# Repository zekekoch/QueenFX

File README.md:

# QueenFX

LED effects for the Queen art car. A Teensy 3.2 drives 16 LED tubes
with FastLED. Effects are selected from the dashboard's 8 lit
buttons (but supports 16), which are read through a 4067 multiplexer and lit by
TLC59711 LED drivers.

## Files

- `QueenFX.ino`: the main sketch. It holds the tube layout, the
  effects, and the button-to-effect mapping in `loop()`.
- `Buttons.h`: dashboard buttons. It reads them through the mux and
  sets their colors through the TLC59711 boards.
- `Mux.h`: reads the 4067 multiplexer that the buttons and dials are
  wired to.
- `hardware/`: the controller board (QueenController 2022b), in Eagle
  9.6 format.
  - `queencontroller2022.sch`: schematic.
  - `queencontroller2022.brd`: board layout.
  - `queencontroller2022.pdf`: a mirrored print of the board layout,
    from Apr 10, 2022. The `.brd` was edited after that (Aug 7, 2022),
    so the print may not match it.

## Setup

### 1. Arduino IDE

Install [Arduino IDE 2.x](https://www.arduino.cc/en/software).

### 2. Teensyduino (Teensy board support)

1. Open **Arduino IDE → Settings** (Preferences on Windows/Linux).
2. Add this URL to **Additional boards manager URLs**:

   ```
   https://www.pjrc.com/teensy/package_teensy_index.json
   ```

3. Open **Tools → Board → Boards Manager**, search for **Teensy**, and
   install **Teensy (for Arduino IDE 2.0.4 or later)**.

PJRC's instructions are at
<https://www.pjrc.com/teensy/td_download.html>.

### 3. Libraries

Install these from **Tools → Manage Libraries**:

| Library | Used by | Notes |
|---|---|---|
| FastLED | `QueenFX.ino`, `Buttons.h` | Teensyduino also bundles a copy |
| Adafruit TLC59711 | `Buttons.h` | Install its dependencies when prompted |
| Adafruit BusIO | Adafruit TLC59711 | Usually installed as a dependency |

### 4. Board settings

Under **Tools**, set:

- **Board:** Teensy 3.2 / 3.1
- **USB Type:** Serial
- **Port:** the Teensy's port

Then compile and upload. The Teensy Loader app opens automatically
during upload. If it doesn't program the board, press the button on
the Teensy.

## Hardware notes

- **LED outputs:** FastLED's parallel output on port D and port C
  gives 8 + 8 = 16 outputs (`addLeds<WS2811_PORTD,8>` and
  `addLeds<WS2811_PORTC,8>` in `setup()`).
- **TLC59711 button lights:** 4 chained boards, data on pin 4, clock
  on pin 3.
- **4067 mux:** select pins A=17, B=18, C=A11, D=19; signal pin Z=A2.
- **Serial monitor:** 57600 baud.

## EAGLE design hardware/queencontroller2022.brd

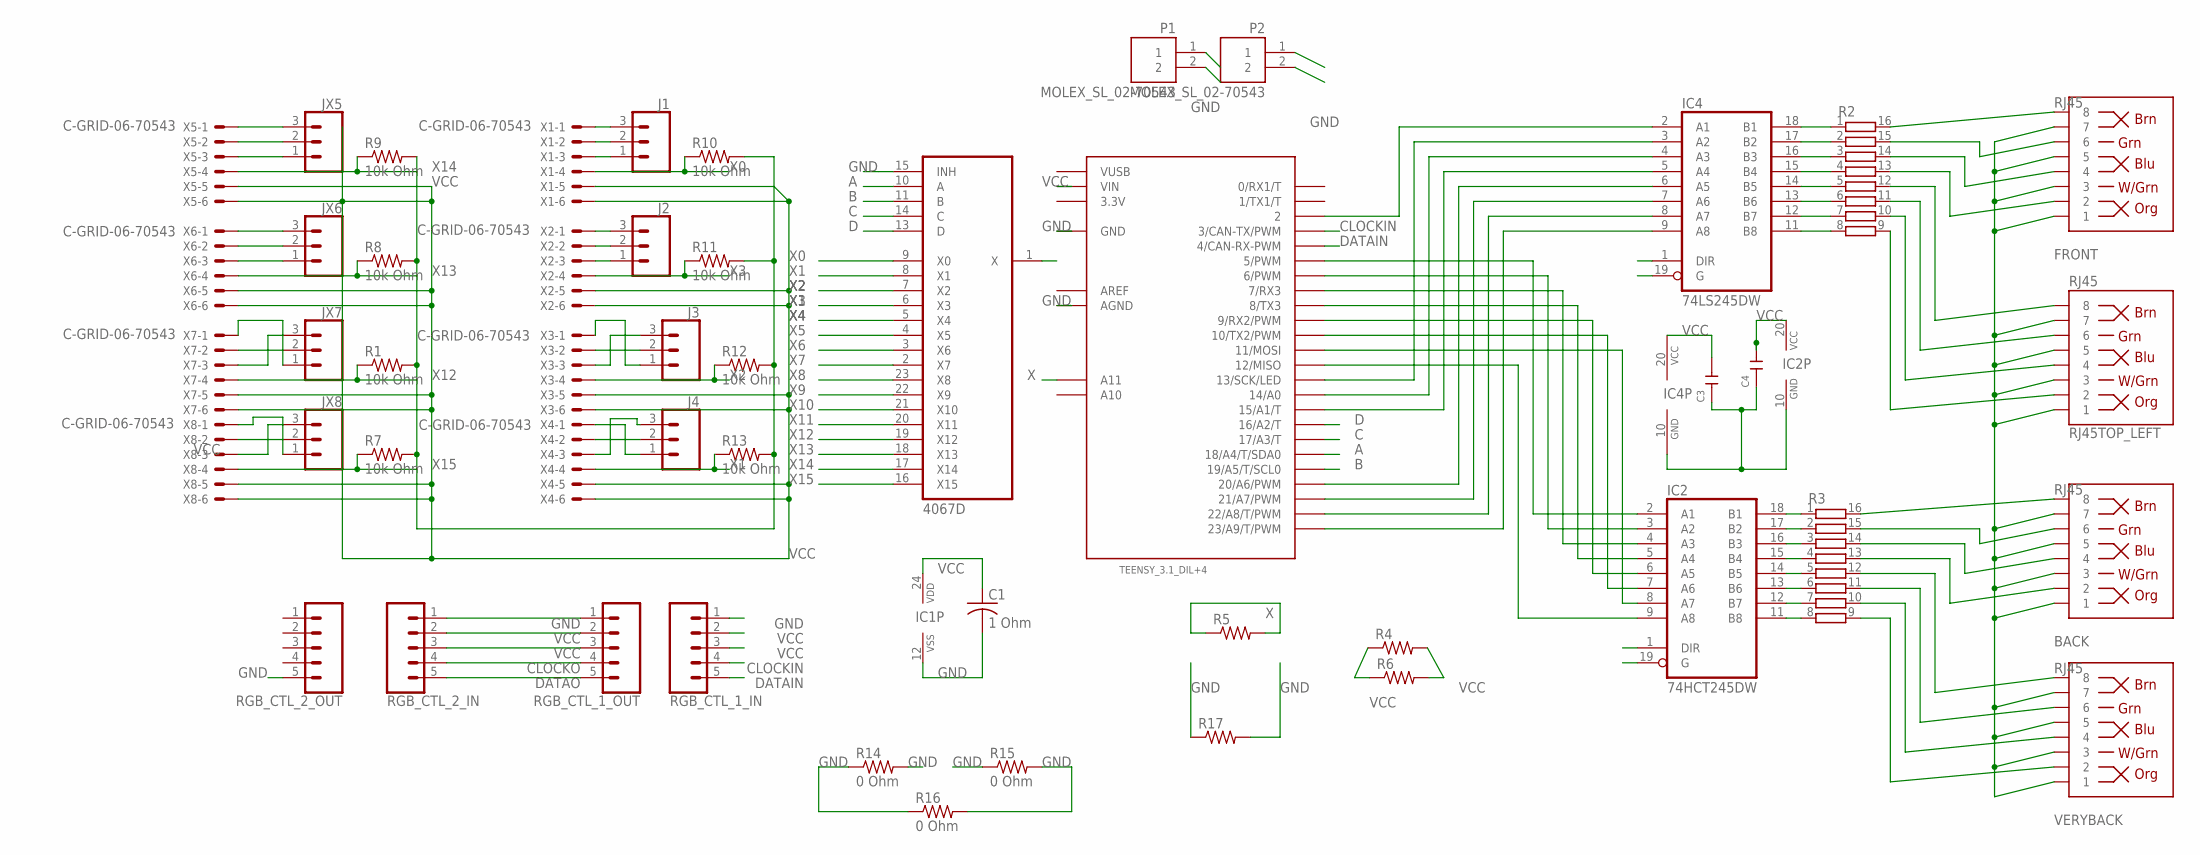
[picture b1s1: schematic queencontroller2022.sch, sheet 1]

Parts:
BACK: RJ45; RJ45-8
C1: 1 Ohm; C1206
C3, C4: CAP-1206; C1206
FRONT: RJ45; RJ45-8
IC1: 4067D; SO24W
IC2: 74HCT245DW; SO20W
IC4: 74LS245DW; SO20W
J1, J2, J3, J4: CONN_03; 1X03
JX5, JX6, JX7, JX8: CONN_03; 1X03
P1, P2: MOLEX_SL_02-70543; SL_70543_2
R1, R7, R8, R9, R10, R11, R12, R13: 10k Ohm; M1206
R2, R3: 4816P-T01; 4816P
R4, R5, R6, R17: R-US_R2512; R2512
R14, R15: 0 Ohm; R2512
R16: 0 Ohm; M1206
RGB_CTL_1_IN, RGB_CTL_1_OUT, RGB_CTL_2_IN, RGB_CTL_2_OUT: CONN_05; 1X05
RJ45TOP_LEFT: RJ45; RJ45-8
U$3: TEENSY_3.1_DIL+4; TEENSY3-DIL+4
VERYBACK: RJ45; RJ45-8
X1, X2, X3, X4, X5, X6, X7, X8: C-GRID-06-70543; 70543-06

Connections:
3.3V: U$3.3.3V
A: IC1.10 (A), U$3.18/A4 (18/A4/T/SDA0)
AREF: U$3.AREF
B: IC1.11 (B), U$3.19/A5 (19/A5/T/SCL0)
C: IC1.14 (C), U$3.17/A3 (17/A3/T)
CLOCKIN: RGB_CTL_1_IN.4, U$3.3 (3/CAN-TX/PWM)
CLOCKO: RGB_CTL_1_OUT.4, RGB_CTL_2_IN.4
D: IC1.13 (D), U$3.16/A2 (16/A2/T)
DATAIN: RGB_CTL_1_IN.5, U$3.4 (4/CAN-RX-PWM)
DATAO: RGB_CTL_1_OUT.5, RGB_CTL_2_IN.5
GND: BACK.1, BACK.3, BACK.5, BACK.7, C1.2, C3.1, C4.1, FRONT.1, FRONT.3, FRONT.5, FRONT.7, IC1.12 (VSS), IC1.15 (INH), IC2.10 (GND), IC2.19 (G), IC4.10 (GND), IC4.19 (G), P1.2, P2.2, R1.2, R7.2, R8.2, R9.2, R10.2, R11.2, R12.2, R13.2, R14.1, R14.2, R15.1, R15.2, R16.1, R16.2, R17.1, R17.2, RGB_CTL_1_IN.1, RGB_CTL_1_OUT.1, RGB_CTL_2_IN.1, RGB_CTL_2_OUT.5, RJ45TOP_LEFT.1, RJ45TOP_LEFT.3, RJ45TOP_LEFT.5, RJ45TOP_LEFT.7, U$3.AGND, U$3.GND, VERYBACK.1, VERYBACK.3, VERYBACK.5, VERYBACK.7
unnamed: FRONT.8, R2.16
unnamed: FRONT.6, R2.15
unnamed: FRONT.4, R2.14
unnamed: FRONT.2, R2.13
unnamed: R2.10, RJ45TOP_LEFT.4
unnamed: IC2.18 (B1), R3.1
unnamed: R2.12, RJ45TOP_LEFT.8
unnamed: IC4.18 (B1), R2.1
unnamed: BACK.8, R3.16
unnamed: BACK.6, R3.15
unnamed: BACK.4, R3.14
unnamed: BACK.2, R3.13
unnamed: J3.3, X3.3
unnamed: R3.11, VERYBACK.6
unnamed: R3.10, VERYBACK.4
unnamed: R3.9, VERYBACK.2
unnamed: IC4.9 (A8), U$3.23/A9 (23/A9/T/PWM)
unnamed: IC2.9 (A8), U$3.12 (12/MISO)
unnamed: IC2.2 (A1), U$3.5 (5/PWM)
unnamed: IC2.3 (A2), U$3.6 (6/PWM)
unnamed: IC2.4 (A3), U$3.7 (7/RX3)
unnamed: IC2.5 (A4), U$3.8 (8/TX3)
unnamed: IC2.6 (A5), U$3.9 (9/RX2/PWM)
unnamed: IC2.7 (A6), U$3.10 (10/TX2/PWM)
unnamed: IC2.8 (A7), U$3.11 (11/MOSI)
unnamed: IC4.8 (A7), U$3.22/A8 (22/A8/T/PWM)
unnamed: IC4.7 (A6), U$3.21/A7 (21/A7/PWM)
unnamed: IC4.6 (A5), U$3.20/A6 (20/A6/PWM)
unnamed: IC4.5 (A4), U$3.15/A1 (15/A1/T)
unnamed: IC4.4 (A3), U$3.14/A0
unnamed: IC4.3 (A2), U$3.13 (13/SCK/LED)
unnamed: IC4.2 (A1), U$3.2
unnamed: IC4.17 (B2), R2.2
unnamed: IC4.16 (B3), R2.3
unnamed: IC4.15 (B4), R2.4
unnamed: IC4.14 (B5), R2.5
unnamed: IC4.13 (B6), R2.6
unnamed: IC4.12 (B7), R2.7
unnamed: IC4.11 (B8), R2.8
unnamed: R2.9, RJ45TOP_LEFT.2
unnamed: IC2.17 (B2), R3.2
unnamed: IC2.16 (B3), R3.3
unnamed: IC2.15 (B4), R3.4
unnamed: IC2.14 (B5), R3.5
unnamed: IC2.13 (B6), R3.6
unnamed: IC2.12 (B7), R3.7
unnamed: IC2.11 (B8), R3.8
unnamed: J3.1, X3.1
unnamed: JX5.3, X5.1
unnamed: JX5.2, X5.2
unnamed: JX5.1, X5.3
unnamed: J4.1, X4.1
unnamed: JX6.3, X6.1
unnamed: JX6.2, X6.2
unnamed: JX6.1, X6.3
unnamed: JX7.3, X7.3
unnamed: JX7.2, X7.2
unnamed: JX7.1, X7.1
unnamed: J4.3, X4.3
unnamed: JX8.3, X8.3
unnamed: JX8.2, X8.2
unnamed: JX8.1, X8.1
unnamed: R2.11, RJ45TOP_LEFT.6
unnamed: R3.12, VERYBACK.8
unnamed: J4.2, X4.2
unnamed: J3.2, X3.2
unnamed: J2.1, X2.3
unnamed: J2.2, X2.2
unnamed: J2.3, X2.1
unnamed: J1.1, X1.3
unnamed: J1.2, X1.2
unnamed: J1.3, X1.1
VCC: C1.1, C3.2, C4.2, IC1.24 (VDD), IC2.1 (DIR), IC2.20 (VCC), IC4.1 (DIR), IC4.20 (VCC), P1.1, P2.1, R4.1, R4.2, R6.1, R6.2, RGB_CTL_1_IN.2, RGB_CTL_1_IN.3, RGB_CTL_1_OUT.2, RGB_CTL_1_OUT.3, RGB_CTL_2_IN.2, RGB_CTL_2_IN.3, U$3.VIN, X1.5, X1.6, X2.5, X2.6, X3.5, X3.6, X4.5, X4.6, X5.5, X5.6, X6.5, X6.6, X7.5, X7.6, X8.5, X8.6
VUSB: U$3.VUSB
X: IC1.1 (X), R5.1, R5.2, U$3.A11
X0: IC1.9 (X0), R10.1, X1.4
X1: IC1.8 (X1), R13.1, X4.4
X2: IC1.7 (X2), R12.1, X3.4
X3: IC1.6 (X3), R11.1, X2.4
X4: IC1.5 (X4)
X5: IC1.4 (X5)
X6: IC1.3 (X6)
X7: IC1.2 (X7)
X8: IC1.23 (X8)
X9: IC1.22 (X9)
X10: IC1.21 (X10)
X11: IC1.20 (X11)
X12: IC1.19 (X12), R1.1, X7.4
X13: IC1.18 (X13), R8.1, X6.4
X14: IC1.17 (X14), R9.1, X5.4
X15: IC1.16 (X15), R7.1, X8.4

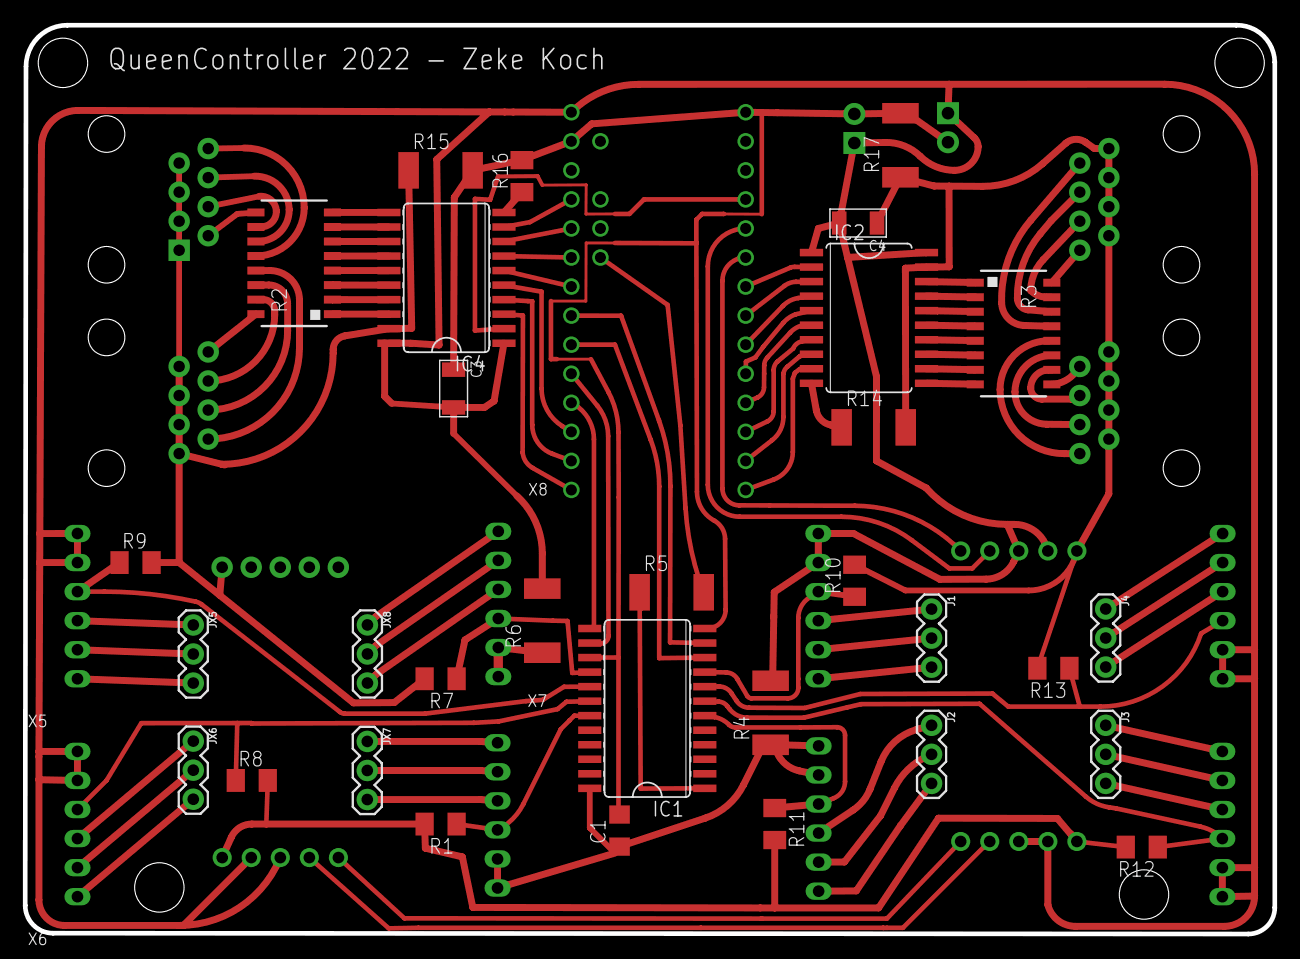
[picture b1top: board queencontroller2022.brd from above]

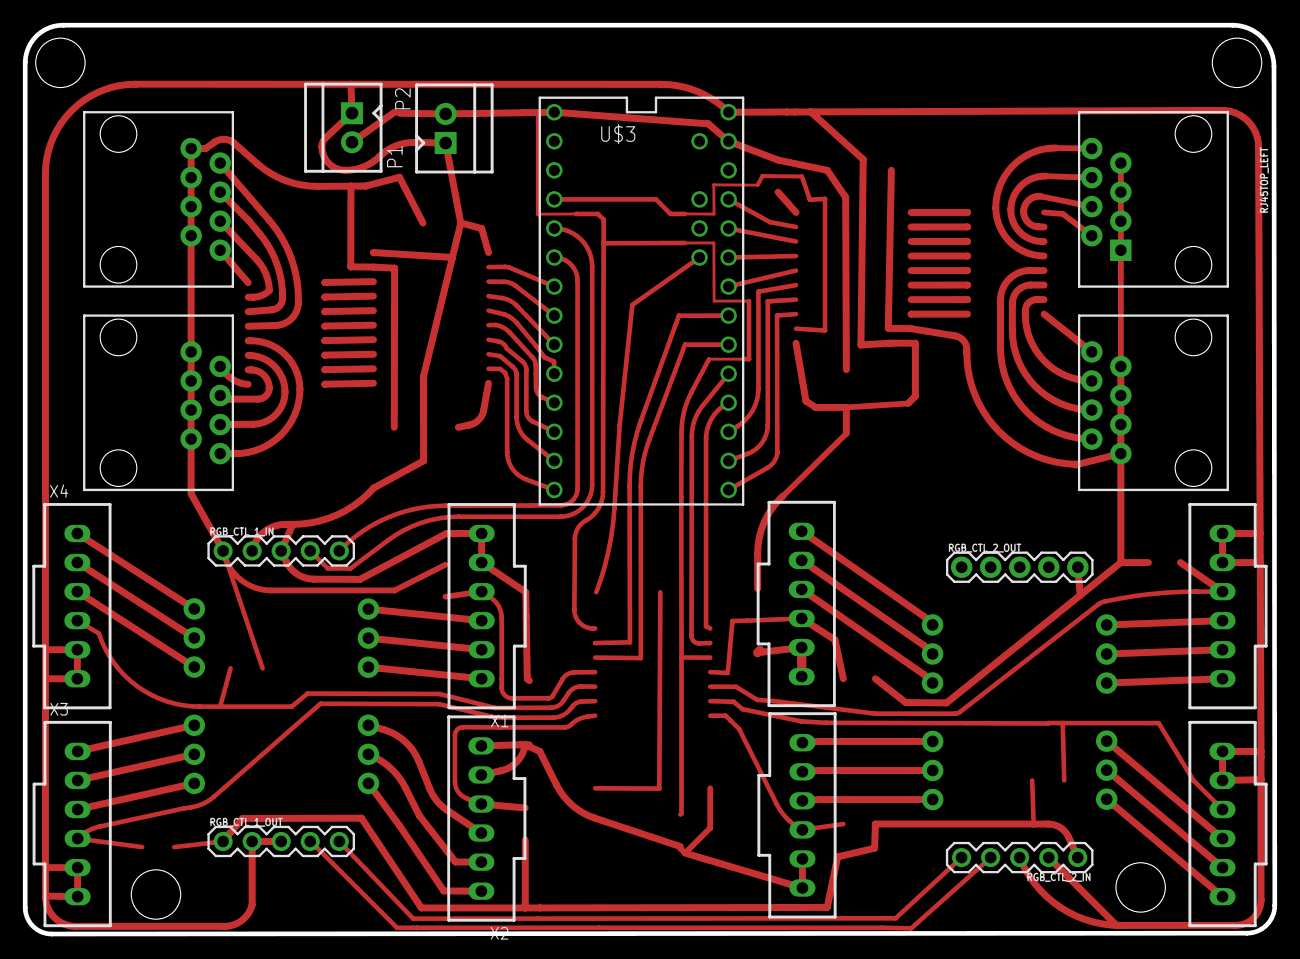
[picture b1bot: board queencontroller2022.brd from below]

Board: 2 copper layers, 109.2 x 79.5 mm, 50 parts (19 on the bottom side), 91 nets.

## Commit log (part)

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2015-08-04 Burningman Art Car 2015
2015-08-08 smoothing and pallets
    Added some smoothing on the dial and buttons
    Added Palette support
    Pulled some animations that weren’t interesting
    Added beginning of Fire animation
2015-08-16 tweaking
    My longest poles only have 139 lights, little tweaks here and there
2015-08-20 virtual mapping
    Created a virtual mapping (12 physical bar, but 14 actual bars)
2015-08-22 improved virtual mapping
    The front lights are now mapped more correctly.
    I’ve also added a couple of new animations (from Mark)
2015-08-23 spiral rainbox, glitter and mirrored fire!
2015-08-24 added cushions, flames in the back
2015-08-29 back cushions working
2015-08-29 most likely final edits
    mapped more stuff to the dashboard controller
2015-09-08 Final BM15 settings
    Control panel was destroyed so I hard coded it to rotating rainbow…
2016-08-22 started doubling lights
    doubled everything (I think) and switched a lot of stuff from bytes to
    ints
    removed the cushions
2016-08-26 interim update for 2016
    cleaned up mapping. my new boards have the strips in a different order
    than fastled so I needed to add another layer of indirection for that.
    I still need to reverse the front ones.
2019-08-10 Update QueenFX.ino
    tweaking before 2019
2019-08-14 Switched to use push buttons instead of my more complex dashboard
2019-08-16 added some new animations
    I added some new animations and switched the buttons from pulldown to pullup
2019-08-23 tweaking which button does which task
2019-08-23 added more animations to the buttons
2019-08-24 getting close
    fixed the tailLights (mapping issue)
    got rid of the dashbaord lights since I'm not using that
    mirrored rotating rainbox
2019-08-24 tube length tweaking
    i'm creeped out that my tubes are different lengths this year... that's not making sense.
2019-09-05 Update QueenFX.ino
    A few final tweaks for tube lengths
2022-04-15 Update QueenFX.ino
    Starting to make changes for 2022. I have a flickering issue likely caused by the libraries loaded into Buttons.h, but I'm not sure yet.
2022-04-16 Update QueenFX.ino
    wow, so after checking all of my electrical, and systematically getting back to the very root of my code I found out that the flickering issue came from a bug in the initializer for FastLED. I now se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
2022-04-16 Update QueenFX.ino
    fixed up the mapping (put the ground effect lights at the back). All the strips are lit up now. I still need to fix the front three lights (they're hard coded and I'm having a little trouble thinking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
2022-05-01 Update QueenFX.ino
    cleaning up the mapping. a couple of gaffs, first I was initializing my mapping arrays incorrectly and I was double mapping the tail lights. Not sure why I was doing that. I removed the second mappin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
2022-05-01 Update QueenFX.ino
    So much progress, but brain dead for the day. Renamed tubeLengths to tubeLength because I kept getting it wrong. Wrote a simple program to test colors, fixed up ShowLeds (mostly fixing off by one err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
2022-05-02 Update QueenFX.ino
    Wow, so I realized that I now have 16 sections of light strips (14 tubes, the tail lights and ground effect lights). I had increased numStrips, but didn't increase the number of entries in tubeLength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
    I also added the ground effect lights (which was easy one I figured out the tail light problem...).
2022-05-02 Update QueenFX.ino
    removed explosion (which I wasn't using and let me get rid of a buffer array) and a little other dead code.
2023-08-08 BM 2022 last minute changes
    Changes made for BM 2022. I haven't reviewed these closely. Terrifying right?
2025-06-02 Fix typo in setup comment

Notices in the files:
parts and their libraries:
SparkFun-Connectors: Licensing: Creative Commons ShareAlike 4.0 International - https://creativecommons.org/licenses/by-sa/4.0
